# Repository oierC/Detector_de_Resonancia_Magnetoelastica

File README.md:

# Detector de Resonancia Magnetoelástica – Archivos del TFG

Este repositorio recopila los principales archivos desarrollados durante mi Trabajo Fin de Grado del Grado en Ingeniería Electrónica sobre el diseño y construcción de un dispositivo Detector de Resonancia Magnetoelástica.

El contenido se organiza en los siguientes tipos de archivos:

* **Arduino:** firmware principal del detector, desarrollado para ESP32. Se encarga del control de todos los elementos hardware del sistema, incluyendo el generador de señal, los convertidores DAC, el potenciómetro digital y la adquisición de datos mediante el ADC. Implementa distintos modos de funcionamiento (control manual, acceso a parámetros de calibración y barridos automáticos), gestionando la generación de campos magnéticos continuos y alternos, la ejecución de barridos en frecuencia y campo magnético, la adquisición de las señales de ganancia y fase, así como la comunicación con el software de control mediante el puerto serie. Además, incorpora comprobaciones de rango y resolución, junto con indicadores luminosos y acústicos para informar del estado del sistema y de posibles errores.

* **Python:** aplicación de escritorio desarrollada para el control del detector y la visualización de resultados. Proporciona una interfaz gráfica (GUI) desde la que es posible configurar los parámetros de medida, establecer barridos de frecuencia del campo magnético alterno y de valor del campo magnético estático, consultar los parámetros de calibración del sistema y comunicarse con el microcontrolador a través del puerto serie. Durante la adquisición de datos recibe en tiempo real las medidas de amplitud y fase, representa gráficamente su evolución, muestra la frecuencia de resonancia para cada valor de campo magnético estático y permite exportar los resultados obtenidos en formato CSV para su posterior análisis. Además, incorpora detección automática de dispositivos compatibles, gestión de errores y notificaciones del estado del sistema.

* **Modelos 3D:** diseños CAD de las piezas de PETG fabricadas para el sistema magnético encargado de generar y medir el campo magnético. Incluye dos soportes para fijar dos solenoides de forma coaxial. Estos soportes integran orificios para la introducción de muestras en el interior del sistema, cavidades para para el acoplamiento de conectores coaxiales y orificios roscantes que permiten fijar los solenoides mediante tornillos. Además, también incluye una tapa para cubrir la soldadura de los conectores y un portamuestras con referencias milimétricas que permiten posicionar las muestras en el interior del sistema.

* **KiCad:** esquema eléctrico y diseño de la placa de circuito impreso (PCB) del prototipo preindustrializado desarrollado para el proyecto. Incluye el generador de señal, circuito de adecuación y amplificación, el detector de ganancia y fase, el sistema de control y procesamiento, un conector USB tipo-C para la comunicación y conectores coaxiales para el sistema magnético.
  
<p align="center">

Este repositorio tiene como objetivo facilitar la consulta, reproducción y reutilización del trabajo realizado, reuniendo en un único lugar tanto el hardware como el software desarrollados para el proyecto.

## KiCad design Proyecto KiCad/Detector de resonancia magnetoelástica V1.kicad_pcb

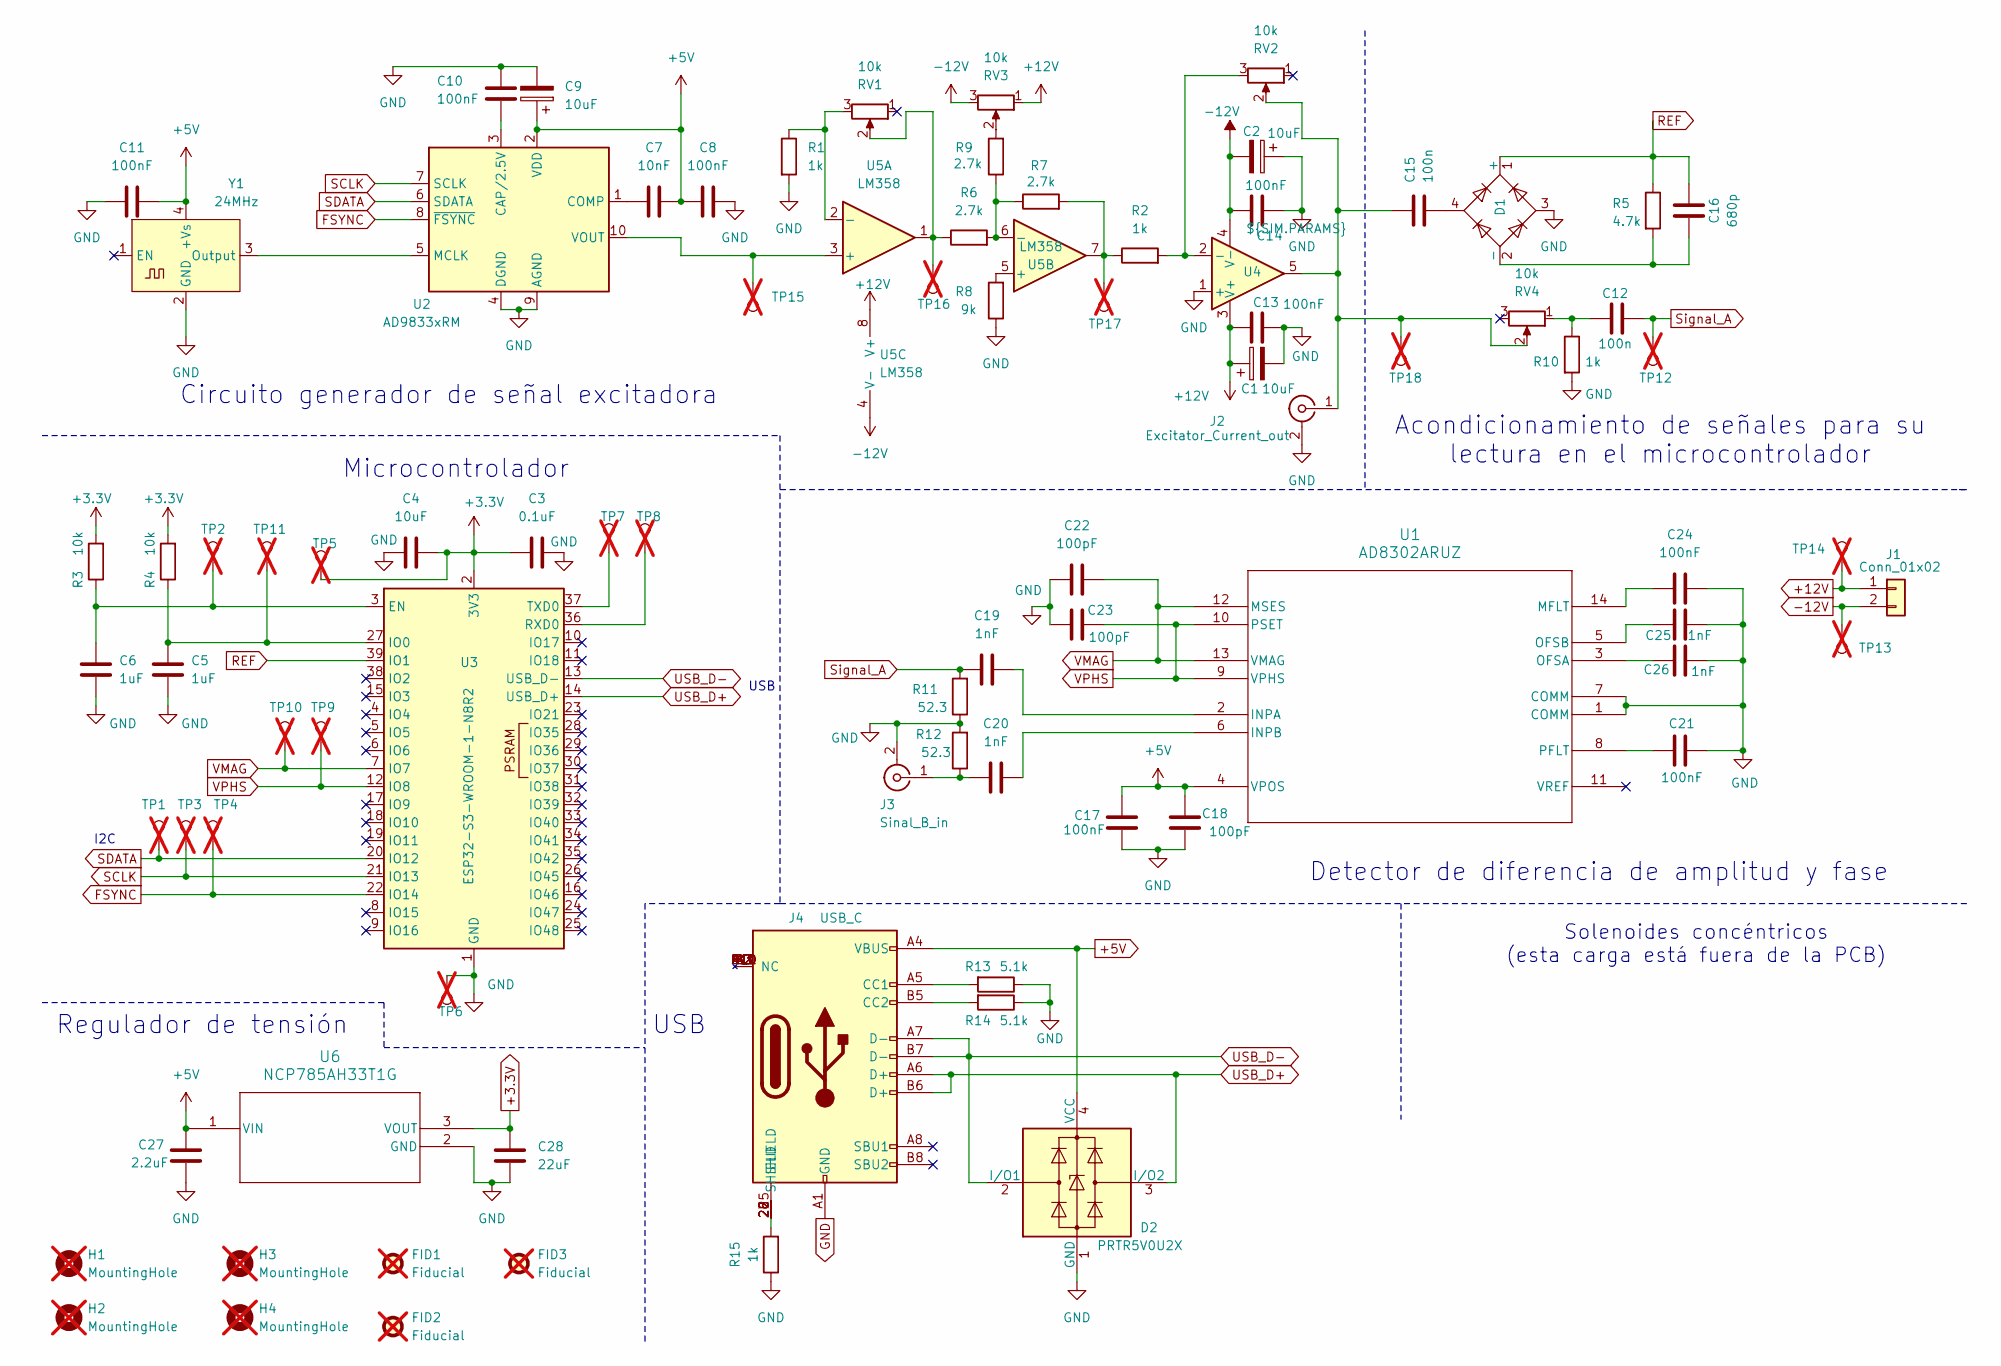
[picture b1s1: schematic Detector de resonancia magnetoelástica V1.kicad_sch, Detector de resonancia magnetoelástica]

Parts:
C1, C2, C4, C9: 10uF; CP_EIA-1608-08_AVX-J
C3: 0.1uF; C_0603_1608Metric
C5, C6: 1uF; C_0603_1608Metric
C7: 10nF; C_0603_1608Metric
C8, C10, C11, C13, C14, C17, C21, C24: 100nF; C_0603_1608Metric
C12, C15: 100n; C_0603_1608Metric
C16: 680p; C_0603_1608Metric
C18, C22, C23: 100pF; C_0603_1608Metric
C19, C20, C25, C26: 1nF; C_0603_1608Metric
C27: 2.2uF; C_0603_1608Metric
C28: 22uF; C_0603_1608Metric
D1: ABS2; Diode_Bridge_Diotec_ABS
D2: PRTR5V0U2X; SOT-143
FID1, FID2, FID3: Fiducial; Fiducial_1mm_Mask2mm; not fitted
H1, H2, H3, H4: MountingHole; MountingHole_3.2mm_M3_DIN965_Pad_TopBottom; not fitted
J1: Conn_01x02; PinSocket_1x02_P2.00mm_Horizontal
J2: Excitator_Current_out; SMA_Molex_73251-2200_Horizontal
J3: Sinal_B_in; SMA_Molex_73251-2200_Horizontal
J4: USB_C; USB_C_Receptacle_GCT_USB4105-xx-A_16P_TopMnt_Horizontal
R1, R2, R10, R15: 1k; R_0603_1608Metric
R3, R4: 10k; R_0603_1608Metric
R5: 4.7k; R_0603_1608Metric
R6, R7, R9: 2.7k; R_0603_1608Metric
R8: 9k; R_0603_1608Metric
R11, R12: 52.3; R_0603_1608Metric
R13, R14: 5.1k; R_0603_1608Metric
RV1, RV2, RV3, RV4: 10k; Potentiometer_ACP_CA6-VSMD_Vertical
TP1, TP2, TP3, TP4, TP5, TP6, TP7, TP8, TP9, TP10, TP11, TP12, TP13, TP14, TP15, TP16, TP17, TP18: TestPoint; TestPoint_Loop_D2.50mm_Drill1.0mm; not fitted
U1: AD8302ARUZ; RU_14_ADI-L
U2: AD9833xRM; MSOP-10_3x3mm_P0.5mm
U3: ESP32-S3-WROOM-1-N8R2; ESP32-S3-WROOM-1
U4: ${SIM.PARAMS}; TO-220-5_P3.4x3.8mm_StaggerOdd_Lead7.13mm_TabDown
U5: LM358; DIP8
U6: NCP785AH33T1G; SOT-89-3_2P7X4P7_ONS-M
Y1: 24MHz; Oscillator_SMD_IQD_IQXO70-4Pin_7.5x5.0mm

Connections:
+3.3V: C3.1, C4.2, C28.1, R3.2, R4.2, TP5.1, U3.2 (3V3), U6.3 (VOUT)
+5V: C7.2, C8.1, C9.1, C11.2, C17.1, C18.1, C27.1, D2.4 (VCC), J4.A4 (VBUS), J4.A9 (VBUS), J4.B4 (VBUS), J4.B9 (VBUS), U1.4 (VPOS), U2.2 (VDD), U6.1 (VIN), Y1.4 (+Vs)
+12V: C1.1, C13.2, J1.1, RV3.1, TP14.1, U4.3 (V+), U5.8 (V+)
-12V: C2.2, C14.2, J1.2, RV3.3, TP13.1, U4.4 (V-), U5.4 (V-)
FSYNC: TP4.1, U2.8 (~FSYNC), U3.22 (IO14)
GND: C1.2, C2.1, C3.2, C4.1, C5.2, C6.2, C8.2, C9.2, C10.2, C11.1, C13.1, C14.1, C17.2, C18.2, C21.2, C22.1, C23.1, C24.2, C25.2, C26.2, C27.2, C28.2, D1.3, D2.1 (GND), J2.2 (Ext), J3.2 (Ext), J4.A1 (GND), J4.A12 (GND), J4.B1 (GND), J4.B12 (GND), R1.2, R8.1, R10.2, R11.1, R12.2, R13.1, R14.1, R15.1, TP6.1, U1.1 (COMM), U1.7 (COMM), U2.4 (DGND), U2.9 (AGND), U3.1 (GND), U3.40 (GND), U3.41 (GND), U4.1 (+), U6.2 (GND), Y1.2 (GND)
unnamed: C12.1, R10.1, RV4.1
unnamed: C15.2, D1.4
unnamed: C16.1, D1.2 (-), R5.2
unnamed: C15.1, J2.1 (In), RV2.2, RV4.2, TP18.1, U4.5
unnamed: C20.1, J3.1 (In), R12.1
unnamed: J4.A5 (CC1), R13.2
unnamed: J4.B5 (CC2), R14.2
unnamed: J4.25 (SHIELD), J4.26 (SHIELD), J4.27 (SHIELD), J4.28 (SHIELD), J4.S1, R15.2
unnamed: R2.1, R7.2, TP17.1, U5.7
unnamed: R6.1, RV1.2, TP16.1, U5.1
unnamed: R9.2, RV3.2
unnamed: C19.2, U1.2 (INPA)
unnamed: C20.2, U1.6 (INPB)
unnamed: C24.1, U1.14 (MFLT)
unnamed: C26.1, U1.3 (OFSA)
unnamed: C25.1, U1.5 (OFSB)
unnamed: C21.1, U1.8 (PFLT)
unnamed: C10.1, U2.3 (CAP/2.5V)
unnamed: C7.1, U2.1 (COMP)
unnamed: U2.5 (MCLK), Y1.3 (Output)
unnamed: TP15.1, U2.10 (VOUT), U5.3 (+)
unnamed: C6.1, R3.1, TP2.1, U3.3 (EN)
unnamed: C5.1, R4.1, TP11.1, U3.27 (IO0)
unnamed: TP8.1, U3.36 (RXD0)
unnamed: TP7.1, U3.37 (TXD0)
unnamed: R2.2, RV2.3, U4.2 (-)
unnamed: R1.1, RV1.3, U5.2 (-)
unnamed: R8.2, U5.5 (+)
unnamed: R6.2, R7.1, R9.1, U5.6 (-)
REF: C16.2, D1.1 (+), R5.1, U3.39 (IO1)
SCLK: TP3.1, U2.7 (SCLK), U3.21 (IO13)
SDATA: TP1.1, U2.6 (SDATA), U3.20 (IO12)
Signal_A: C12.2, C19.1, R11.2, TP12.1
USB_D+: D2.3 (I/O2), J4.A6 (D+), J4.B6 (D+), U3.14 (USB_D+)
USB_D-: D2.2 (I/O1), J4.A7 (D-), J4.B7 (D-), U3.13 (USB_D-)
VMAG: C22.2, TP10.1, U1.12 (MSES), U1.13 (VMAG), U3.7 (IO7)
VPHS: C23.2, TP9.1, U1.9 (VPHS), U1.10 (PSET), U3.12 (IO8)

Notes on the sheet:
Detector de diferencia de amplitud y fase
Circuito generador de señal excitadora
USB
Regulador de tensión
Microcontrolador
I2C
Solenoides concéntricos (esta carga está fuera de la PCB)
USB
Acondicionamiento de señales para su lectura en el microcontrolador

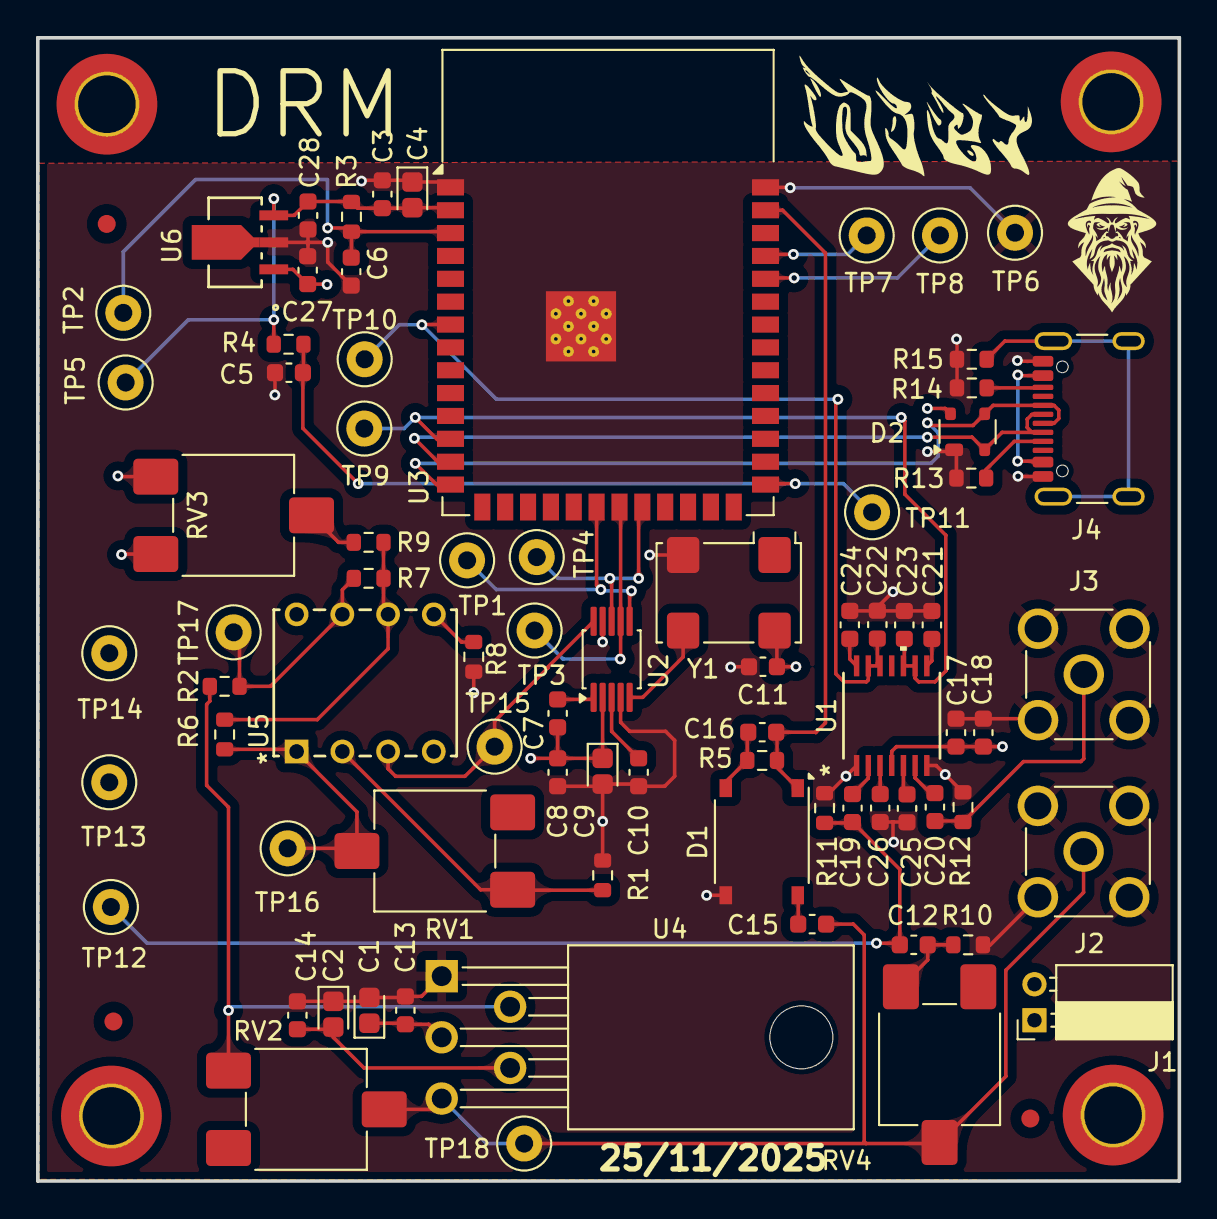
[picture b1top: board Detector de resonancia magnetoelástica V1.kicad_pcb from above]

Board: 4 copper layers, 63.4 x 63.5 mm, 85 parts (0 on the bottom side), 43 nets.

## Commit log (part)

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2026-06-28 Modelos 3D del sistema de solenoides.
